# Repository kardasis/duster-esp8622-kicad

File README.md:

# Duster
This is the kicad schematic and pcb files for the hardware for [duster](https://github.com/kardasis/duster)

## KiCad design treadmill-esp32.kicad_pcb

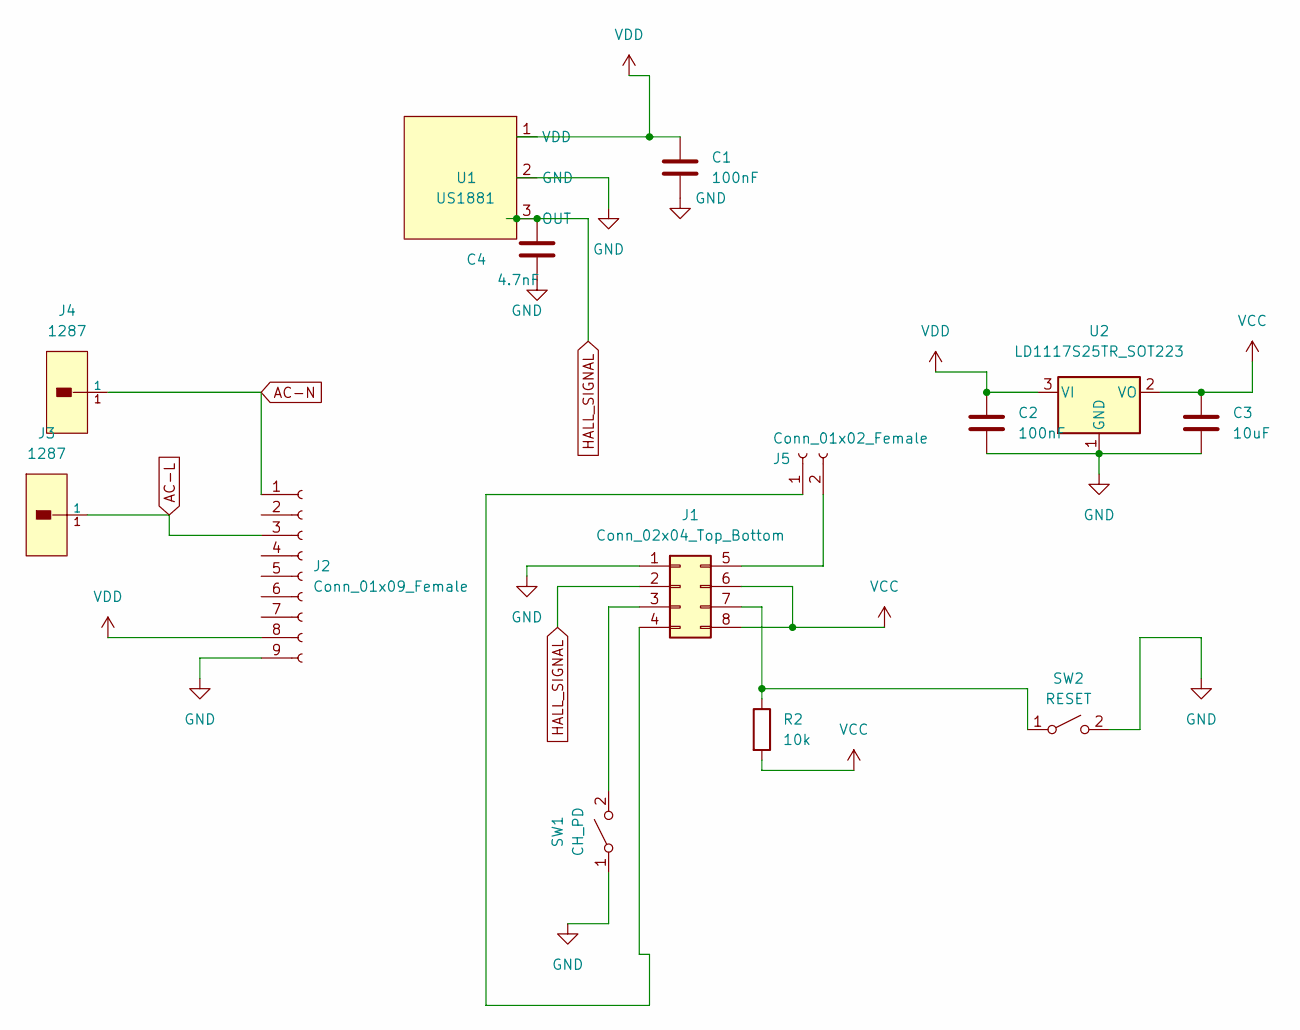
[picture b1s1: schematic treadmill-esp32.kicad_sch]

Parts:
C1, C2: 100nF; C_Disc_D5.0mm_W2.5mm_P5.00mm
C3: 10uF; C_Disc_D5.0mm_W2.5mm_P5.00mm
C4: 4.7nF; C_Disc_D5.0mm_W2.5mm_P5.00mm
J1: Conn_02x04_Top_Bottom; PinHeader_2x04_P2.54mm_Vertical
J2: Conn_01x09_Female; PinSocket_1x09_P2.54mm_Vertical
J3, J4: 1287; Keystone-1287-0-0-0; current rating 20A; mouser part number 534-1287; digikey description TERMINAL QUICKFIT .052\DIA .250\
J5: Conn_01x02_Female; PinHeader_1x02_P2.54mm_Vertical
R2: 10k; R_Axial_DIN0207_L6.3mm_D2.5mm_P7.62mm_Horizontal
SW1: CH_PD; Pushbutton-6mm6mm-5mm_pin
SW2: RESET; Pushbutton-6mm6mm-5mm_pin
U1: US1881; TO-92S
U2: LD1117S25TR_SOT223; TO-220-3_Vertical

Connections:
AC-L: J2.3, J3.1
AC-N: J2.1, J4.1
GND: C1.1, C2.2, C3.2, C4.1, J1.1, J2.9, SW1.1 (A), SW2.2 (B), U1.2 (GND), U2.1 (GND)
HALL_SIGNAL: C4.2, J1.2, U1.3 (OUT)
unnamed: J1.3, SW1.2 (B)
unnamed: J1.4, J5.1
unnamed: J1.5, J5.2
unnamed: J1.7, R2.1, SW2.1 (A)
VCC: C3.1, J1.6, J1.8, R2.2, U2.2 (VO)
VDD: C1.2, C2.1, J2.8, U1.1 (VDD), U2.3 (VI)

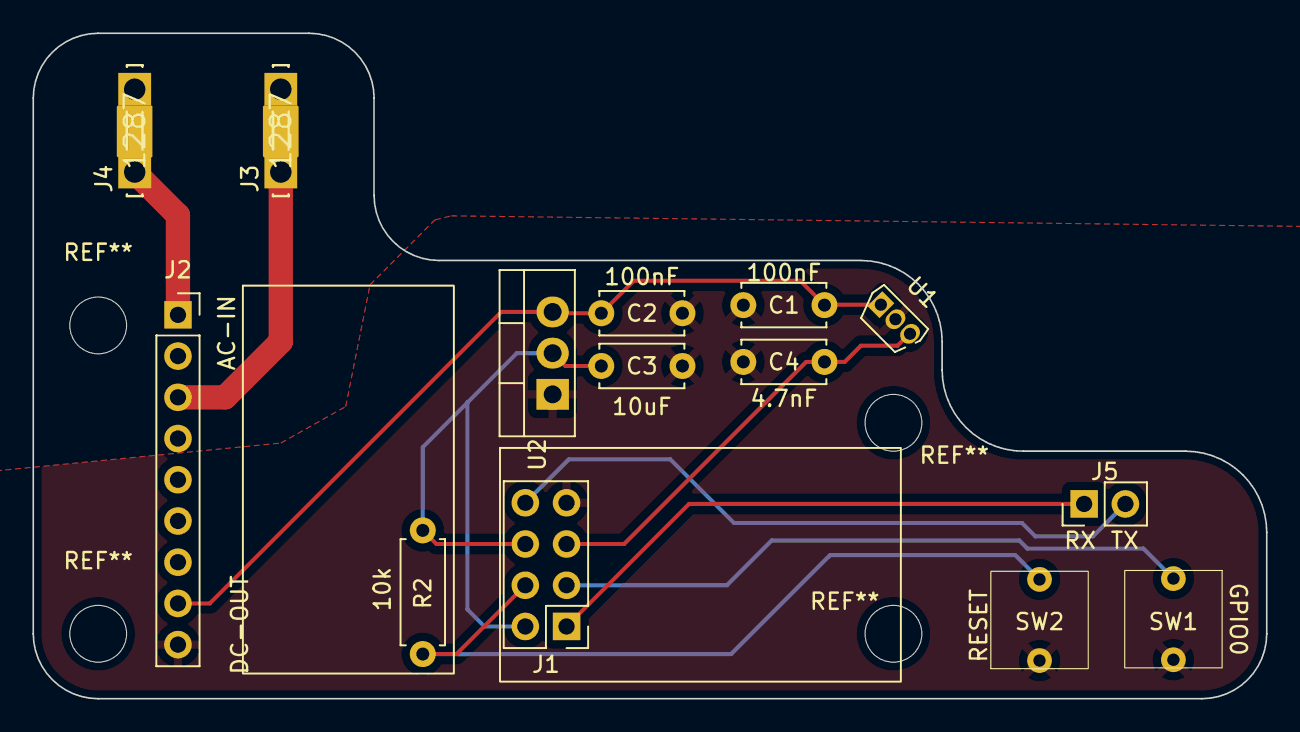
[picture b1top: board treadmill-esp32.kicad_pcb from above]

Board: 2 copper layers, 76.0 x 41.0 mm, 14 parts (0 on the bottom side), 10 nets.

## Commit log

2022-08-12 add to gitignore
2022-08-12 add basic readme
